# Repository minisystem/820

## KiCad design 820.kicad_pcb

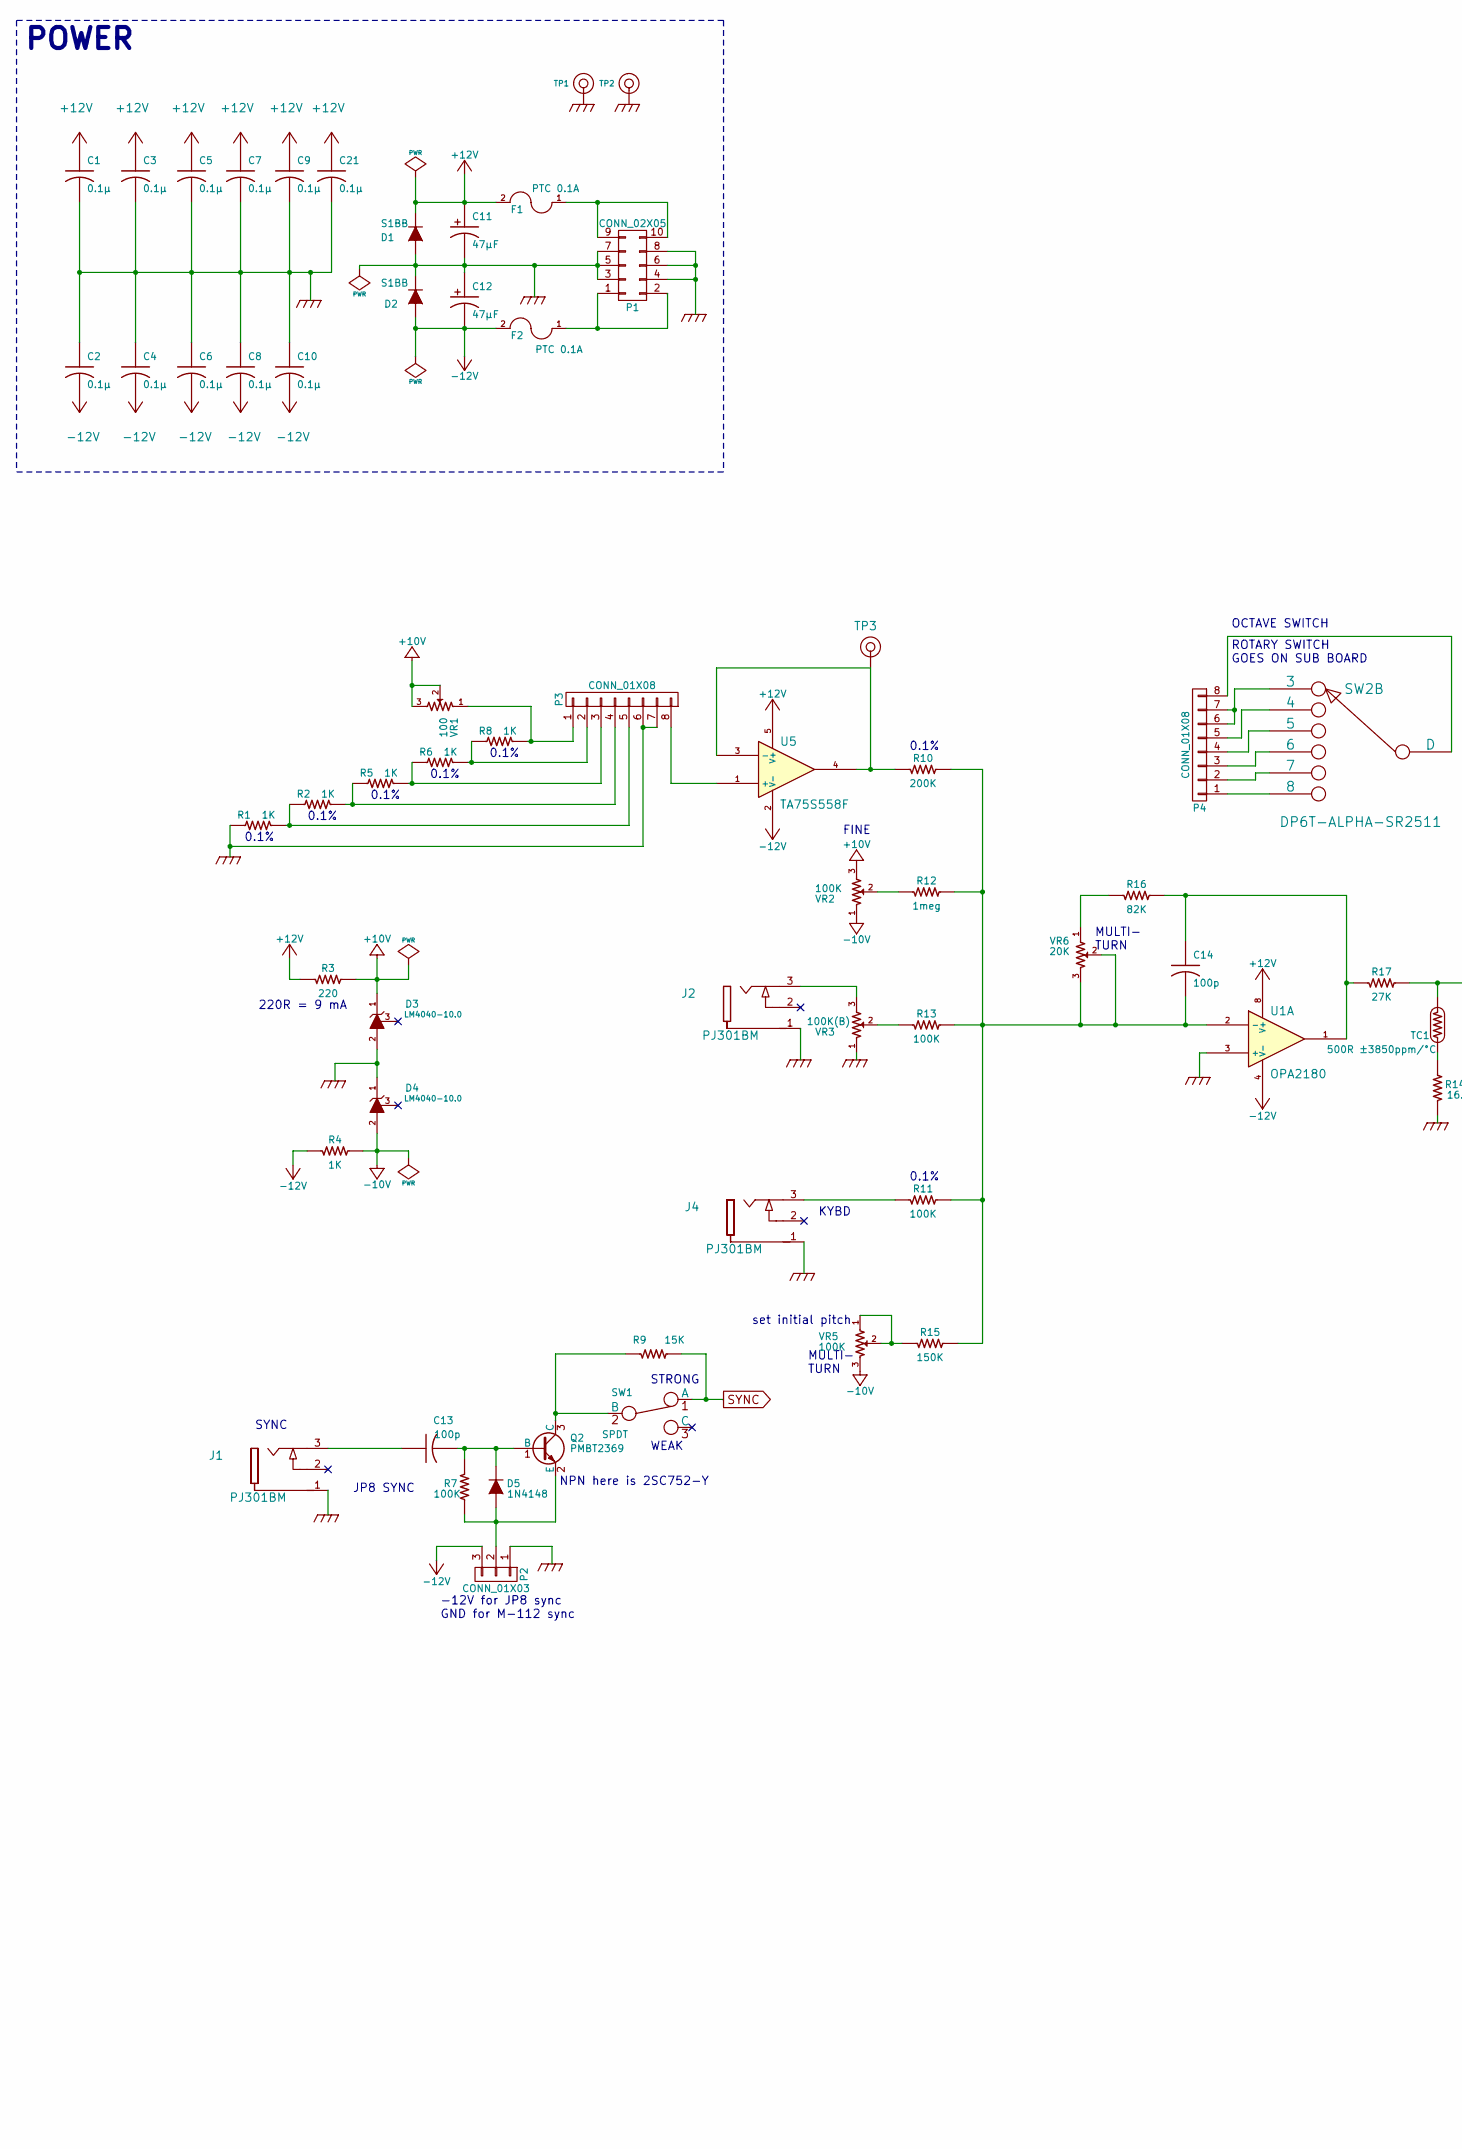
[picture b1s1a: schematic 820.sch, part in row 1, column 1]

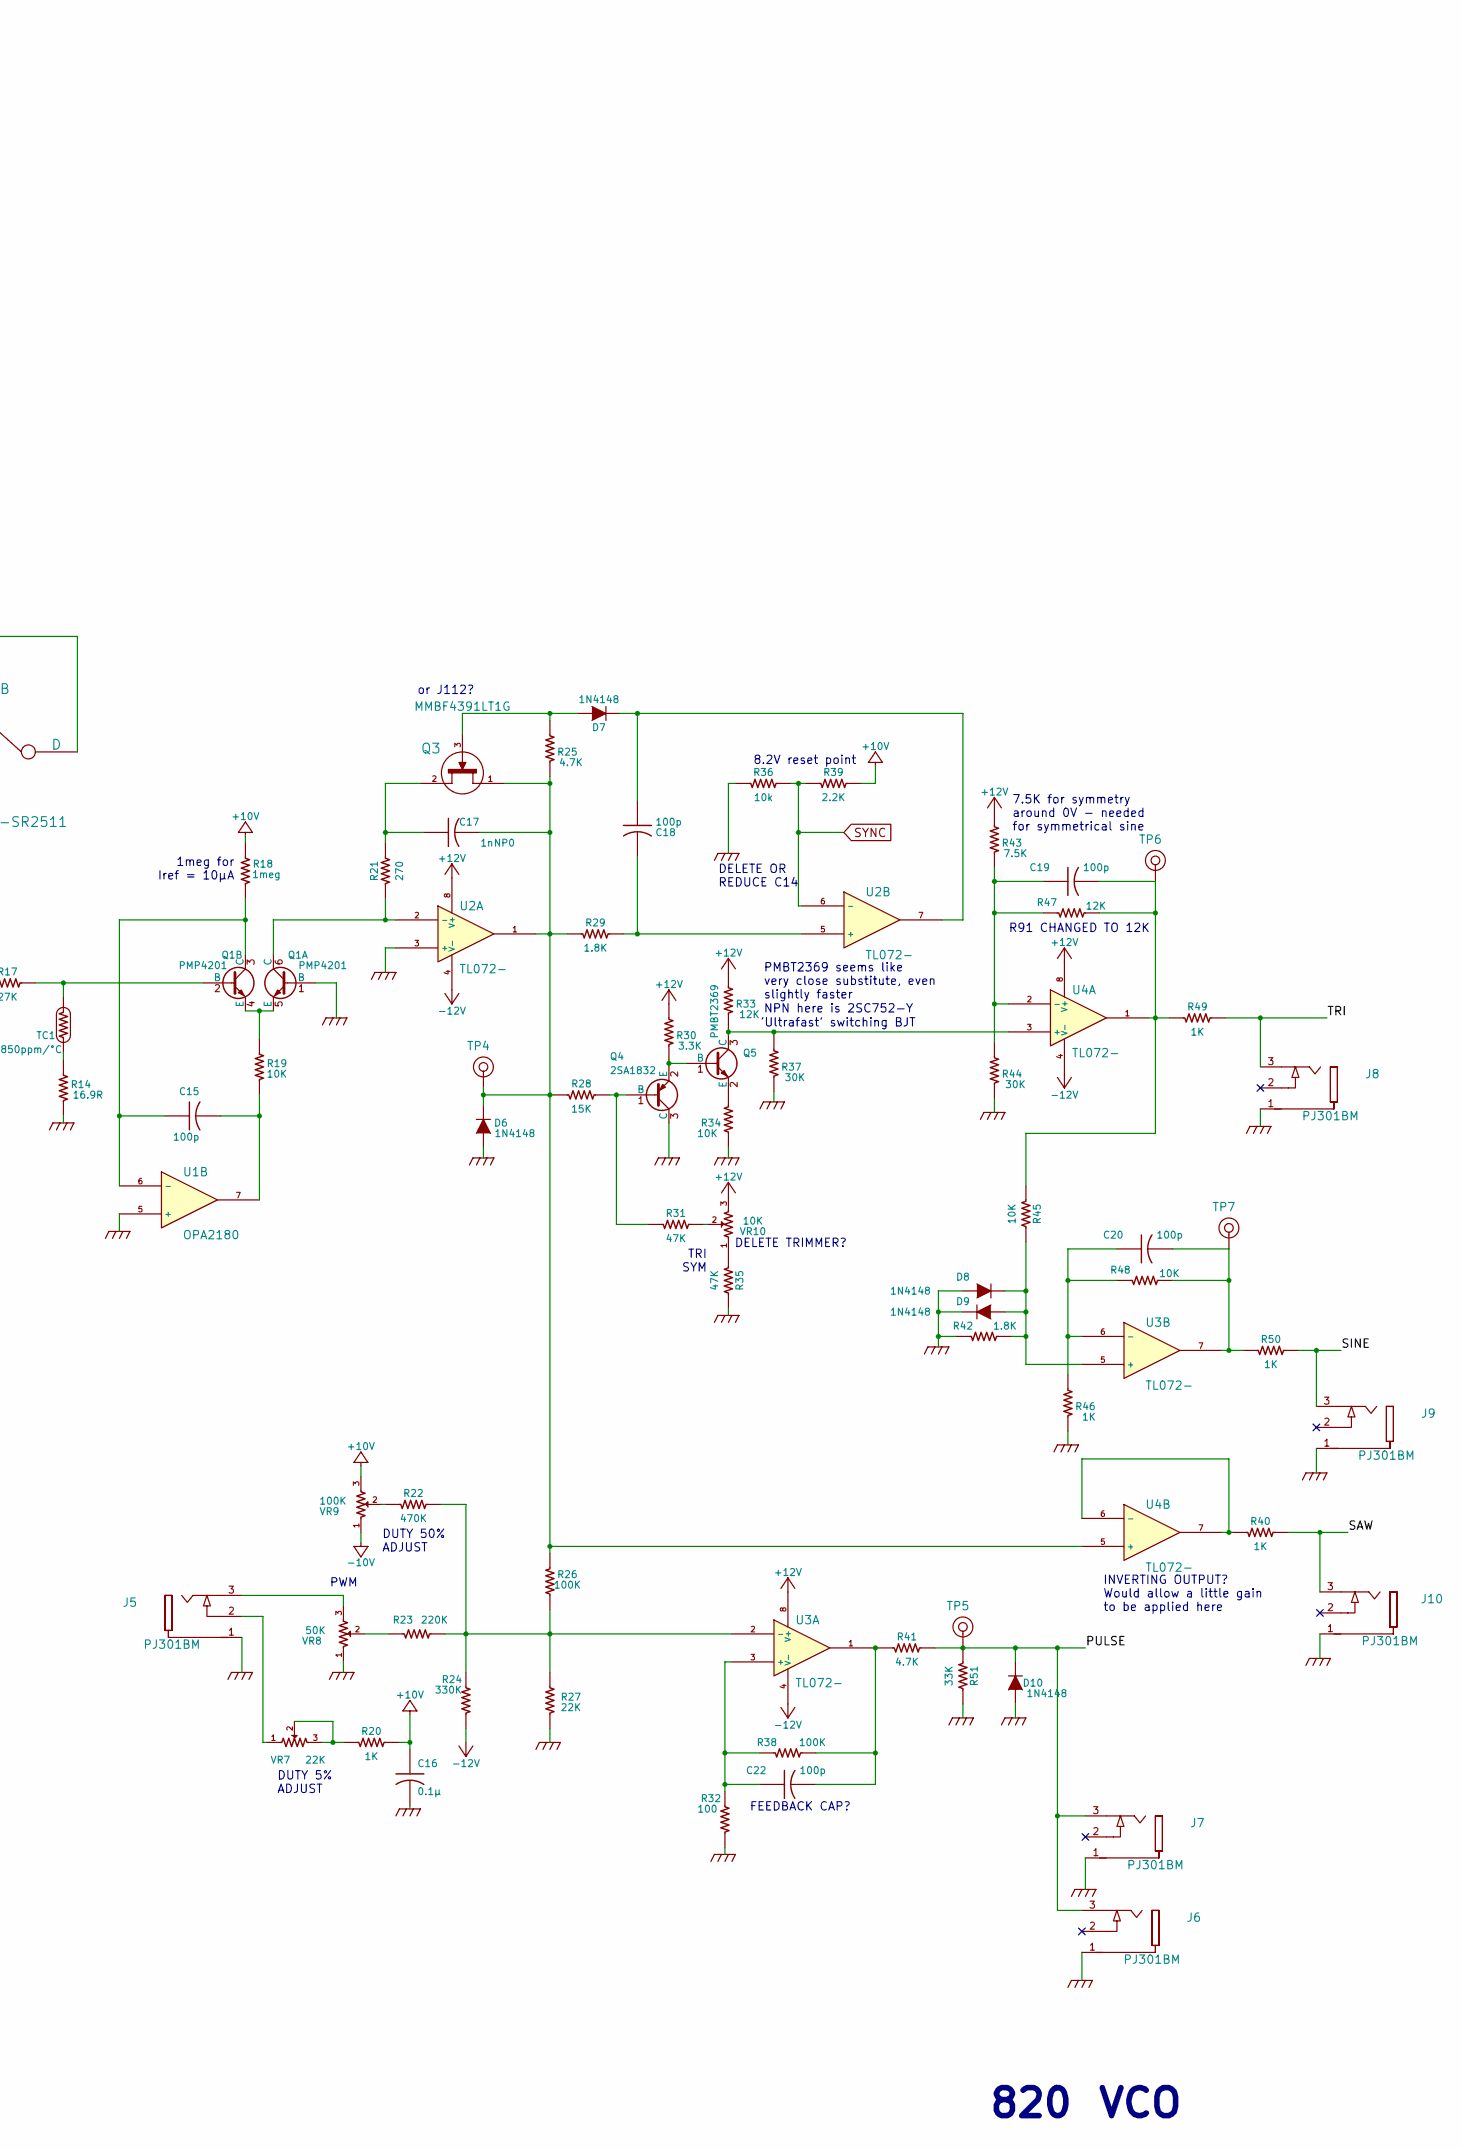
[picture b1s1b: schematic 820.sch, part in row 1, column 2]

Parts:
C1, C2, C3, C4, C5, C6, C7, C8, C9, C10, C16, C21: 0.1µ; SM0603-C-JRL
C11, C12: 47μF; jrl_c_elec_5x5.3
C13, C18, C19, C20, C22: 100p; SM0603-C-JRL
C14, C15: 100p; SM0603-C-JRL; Digikey 399-1122-1-ND
C17: 1n; SM0603-C-JRL
D1, D2: S1BB; SMB-1C2A
D3, D4: LM4040-10.0; SOT23-132-JRL
D5, D6, D7, D8, D9, D10: 1N4148; SOD323-C1A2
F1, F2: PTC 0.1A; C_0805
J1, J2, J4, J5, J6, J7, J8, J9, J10: PJ301BM; PJ-301B-JACK-SLOTS
P1: CONN_02X05; Pin_Header_Straight_2x05_Pitch2.54mm
P2: CONN_01X03; Pin_Header_Straight_1x03_Pitch2.54mm
P3, P4: CONN_01X08; Pin_Header_Straight_1x08_Pitch2.54mm
Q1: PMP4201; SOT-666
Q2: PMBT2369; SOT-23
Q3: MMBF4391LT1G; SOT23-132-JRL
Q4: 2SA1832; SOT416-SC75
Q5: PMBT2369; SOT23-132-JRL
R1, R2, R5, R6, R8: 1K; SM0603-R-JRL
R3: 220; SM0603-R-JRL; Digikey P10.0KCCT-ND
R4, R20, R40, R46, R49, R50: 1K; SM0603-R-JRL; Digikey P10.0KCCT-ND
R7, R26, R38: 100K; SM0603-R-JRL; Digikey P10.0KCCT-ND
R9, R28: 15K; SM0603-R-JRL; Digikey P10.0KCCT-ND
R10: 200K; SM0603-R-JRL; Digikey P91.0KCCT-ND
R11, R13: 100K; SM0603-R-JRL; Digikey P91.0KCCT-ND
R12: 1meg; SM0603-R-JRL; Digikey P91.0KCCT-ND
R14: 16.9R; SM0603-R-JRL; Digikey P10.0KCCT-ND
R15: 150K; SM0603-R-JRL; Digikey P91.0KCCT-ND
R16: 82K; SM0603-R-JRL; Digikey P91.0KCCT-ND
R17: 27K; SM0603-R-JRL; Digikey P56.0KCCT-ND
R18: 1meg; SM0603-R-JRL; Digikey P1.50MCCT-ND
R19, R34, R45, R48: 10K; SM0603-R-JRL; Digikey P10.0KCCT-ND
R21: 270; SM0603-R-JRL; Digikey P10.0KCCT-ND
R22: 470K; SM0603-R-JRL; Digikey P10.0KCCT-ND
R23: 220K; SM0603-R-JRL; Digikey P10.0KCCT-ND
R24: 330K; SM0603-R-JRL; Digikey P10.0KCCT-ND
R25, R41: 4.7K; SM0603-R-JRL; Digikey P10.0KCCT-ND
R27: 22K; SM0603-R-JRL
R29, R42: 1.8K; SM0603-R-JRL; Digikey P10.0KCCT-ND
R30: 3.3K; SM0603-R-JRL; Digikey P10.0KCCT-ND
R31, R35: 47K; SM0603-R-JRL; Digikey P10.0KCCT-ND
R32: 100; SM0603-R-JRL; Digikey P10.0KCCT-ND
R33, R47: 12K; SM0603-R-JRL; Digikey P10.0KCCT-ND
R36: 10k; SM0603-R-JRL; Digikey P10.0KCCT-ND
R37, R44: 30K; SM0603-R-JRL; Digikey P10.0KCCT-ND
R39: 2.2K; SM0603-R-JRL; Digikey P10.0KCCT-ND
R43: 7.5K; SM0603-R-JRL; Digikey P10.0KCCT-ND
R51: 33K; SM0603-R-JRL; Digikey P10.0KCCT-ND
SW1: SPDT; SS-12F108-1P2T-SLIDE
SW2: DP6T-ALPHA-SR2511; SR2511-ALPHA
TC1: 500R ±3850ppm/°C; SM0603-R-JRL
TP1, TP2: CONN_1; TEST_POINT_LOOP_4592
TP3, TP4, TP5, TP6, TP7: TEST_POINT; TEST_POINT_5000_SERIES
U1: OPA2180; MSOP-8_3x3mm_Pitch0.65mm
U2, U3, U4: TL072-; TSSOP8-JRL
U5: TA75S558F; SOT753_TSOP5_SC-74A
VR1: 100; TC33X-2
VR2: 100K; RD901F-ALPHA-POT-T18
VR3: 100K(B); RD901F-ALPHA-POT-T18
VR5: 100K; Bourns-3296W
VR6: 20K; Bourns-3296W
VR7: 22K; TC33X-2
VR8: 50K; RD901F-ALPHA-POT-T18
VR9: 100K; TC33X-2
VR10: 10K; TC33X-2

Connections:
+10V: C16.1, D3.1 (K), R3.2, R18.2, R20.2, R39.2, VR1.2, VR1.3, VR2.3, VR9.3
+12V: C1.1, C3.1, C5.1, C7.1, C9.1, C11.1 (+), C21.1, D1.1 (K), F1.2, R3.1, R30.2, R33.2, R43.2, U1.8 (V+), U2.8 (V+), U3.8 (V+), U4.8 (V+), U5.5 (V+), VR10.3
-10V: D4.2 (A), R4.2, VR2.1, VR5.3, VR9.1
-12V: C2.2, C4.2, C6.2, C8.2, C10.2, C12.2 (-), D2.2 (A), F2.2, P2.3, R4.1, R24.2, U1.4 (V-), U2.4 (V-), U3.4 (V-), U4.4 (V-), U5.2 (V-)
/PULSE: D10.1 (K), J6.3, J7.3, R41.2, R51.1, TP5.1
/SAW: J10.3, R40.2
/SINE: J9.3, R50.2
/TRI: J8.3, R49.2
GND: C1.2, C2.1, C3.2, C4.1, C5.2, C6.1, C7.2, C8.1, C9.2, C10.1, C11.2 (-), C12.1 (+), C16.2, C21.2, D1.2 (A), D2.1 (K), D3.2 (A), D4.1 (K), D6.2 (A), D8.2 (A), D9.1 (K), D10.2 (A), J1.1, J2.1, J4.1, J5.1, J6.1, J7.1, J8.1, J9.1, J10.1, P1.3, P1.4, P1.5, P1.6, P1.7, P1.8, P2.1, P3.6, P3.7, Q1.1 (B), Q4.3 (C), R1.2, R14.1, R27.1, R32.2, R34.1, R35.1, R36.1, R37.1, R42.1, R44.1, R46.1, R51.2, TP1.1, TP2.1, U1.3 (+), U1.5 (+), U2.3 (+), VR3.1, VR8.1
unnamed: C13.1, J1.3
unnamed: C13.2, D5.1 (K), Q2.1 (B), R7.2
unnamed: C14.1, R16.2, R17.1, U1.1
unnamed: C14.2, R10.2, R11.2, R12.2, R13.2, R15.2, U1.2 (-), VR6.2, VR6.3
unnamed: C15.1, Q1.3 (C), R18.1, U1.6 (-)
unnamed: C15.2, R19.1, U1.7
unnamed: C17.1, Q3.2 (S), R21.2
unnamed: C17.2, D6.1 (K), Q3.1 (D), R25.1, R26.1, R28.1, R29.1, TP4.1, U2.1, U4.5 (+)
unnamed: C18.1, D7.1 (K), U2.7
unnamed: C18.2, R29.2, U2.5 (+)
unnamed: C19.1, R43.1, R44.2, R47.1, U4.2 (-)
unnamed: C19.2, R45.1, R47.2, R49.1, TP6.1, U4.1
unnamed: C20.1, R46.2, R48.1, U3.6 (-)
unnamed: C20.2, R48.2, R50.1, TP7.1, U3.7
unnamed: C22.1, R32.1, R38.1, U3.3 (+)
unnamed: C22.2, R38.2, R41.1, U3.1
unnamed: D5.2 (A), P2.2, Q2.2 (E), R7.1
unnamed: D7.2 (A), Q3.3 (G), R25.2
unnamed: D8.1 (K), D9.2 (A), R42.2, R45.2, U3.5 (+)
unnamed: F1.1, P1.9, P1.10
unnamed: F2.1, P1.1, P1.2
unnamed: J2.3, VR3.3
unnamed: J4.3, R11.1
unnamed: J5.2, VR7.1
unnamed: J5.3, VR8.3
unnamed: P3.1, R8.1, VR1.1
unnamed: P3.2, R6.1, R8.2
unnamed: P3.3, R5.1, R6.2
unnamed: P3.4, R2.1, R5.2
unnamed: P3.5, R1.1, R2.2
unnamed: P3.8, U5.1 (+)
unnamed: P4.1, SW2.8
unnamed: P4.2, SW2.7
unnamed: P4.3, SW2.6
unnamed: P4.4, SW2.5
unnamed: P4.5, SW2.4
unnamed: P4.6, P4.7, SW2.3
unnamed: P4.8, SW2.D
unnamed: Q1.2 (B), R17.2, TC1.1
unnamed: Q1.4 (E), Q1.5 (E), R19.2
unnamed: Q1.6 (C), R21.1, U2.2 (-)
unnamed: Q2.3 (C), R9.1, SW1.2 (B)
unnamed: Q4.1 (B), R28.2, R31.2
unnamed: Q4.2 (E), Q5.1 (B), R30.1
unnamed: Q5.2 (E), R34.2
unnamed: Q5.3 (C), R33.1, R37.2, U4.3 (+)
unnamed: R10.1, TP3.1, U5.3 (-), U5.4
unnamed: R12.1, VR2.2
unnamed: R13.1, VR3.2
unnamed: R14.2, TC1.2
unnamed: R15.1, VR5.1, VR5.2
unnamed: R16.1, VR6.1
unnamed: R20.1, VR7.2, VR7.3
unnamed: R22.1, VR9.2
unnamed: R22.2, R23.2, R24.1, R26.2, R27.2, U3.2 (-)
unnamed: R23.1, VR8.2
unnamed: R31.1, VR10.2
unnamed: R35.2, VR10.1
unnamed: R40.1, U4.6 (-), U4.7
SYNC: R9.2, R36.2, R39.1, SW1.1 (A), U2.6 (-)

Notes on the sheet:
or J112?
VCO
NPN here is 2SC752-Y
8.2V reset point
'Ultrafast' switching BJT
PMBT2369 seems like very close substitute, even slightly faster
MULTI- TURN
set initial pitch
FINE
DUTY 50% ADJUST
DUTY 5% ADJUST
PWM
SYNC
ROTARY SWITCH GOES ON SUB BOARD
JP8 SYNC
WEAK
STRONG
-12V for JP8 sync GND for M-112 sync
OCTAVE SWITCH
TRI SYM
DELETE TRIMMER?
DELETE OR REDUCE C14
220R = 9 mA
0.1%
1meg for Iref = 10µA
R91 CHANGED TO 12K
7.5K for symmetry around 0V - needed for symmetrical sine
POWER
KYBD
820
INVERTING OUTPUT? Would allow a little gain to be applied here
FEEDBACK CAP?

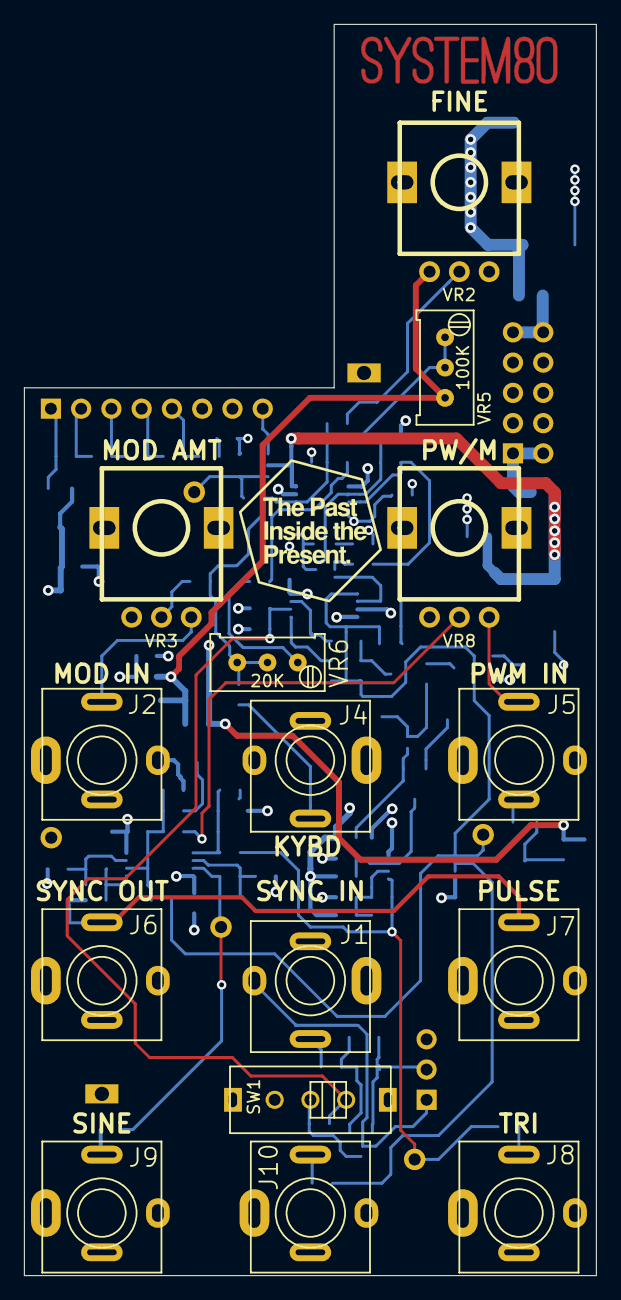
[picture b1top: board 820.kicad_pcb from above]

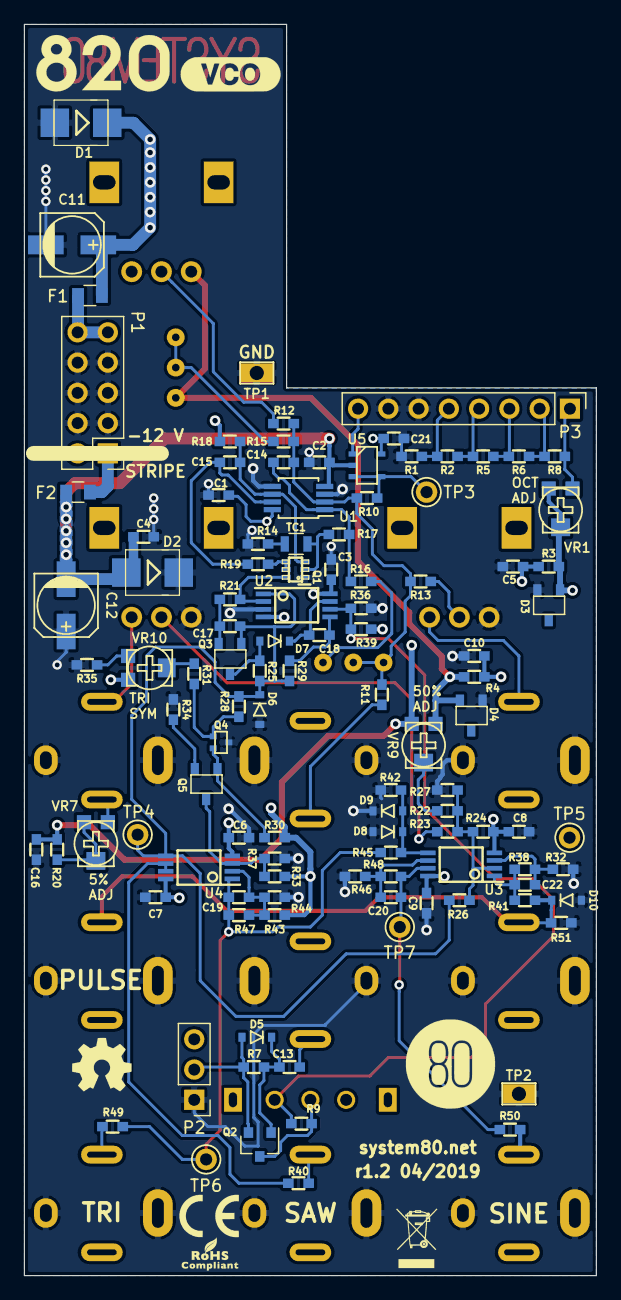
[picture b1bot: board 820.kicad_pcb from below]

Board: 4 copper layers, 48.0 x 105.0 mm, 125 parts (110 on the bottom side), 62 nets.

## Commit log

2018-07-26 starting to place and route
2018-07-27 mostly placed
2018-07-30 routed, except for rotary switch on separate daughter board
2018-07-30 separated rotary switch daughter board, finished routing
2018-08-02 bit of tweaking, need to start placing references
2018-08-28 arranged silk screen references
2018-10-21 fixed incorrect pin on switch board: 9 was connected instead of 8
2018-10-24 changed 2SC4207 NPN pair to BCM847 matched pair.
2018-10-31 PMP4201 NPN matched pair replaces BCM847
2018-11-20 adding panel files
2019-03-22 first commit in a while. switched matched pair to PMP and other stuff. getting ready to order r1.1
2019-03-27 updates for final prototype, changed matched pair back to SOT-363
2019-03-28 gerbers ready to submit to pcb fab house. need to generate gerbers for rotary switch board still
2019-04-12 final prototype ordred, built and tested, committing now and then branching to panelization
2019-04-12 added panelized PCB
2019-04-13 edits to panelized, fiduicals and border added
